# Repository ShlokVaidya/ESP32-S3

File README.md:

# ESP32-S3

Unfortunately the parts required require standard PCBA

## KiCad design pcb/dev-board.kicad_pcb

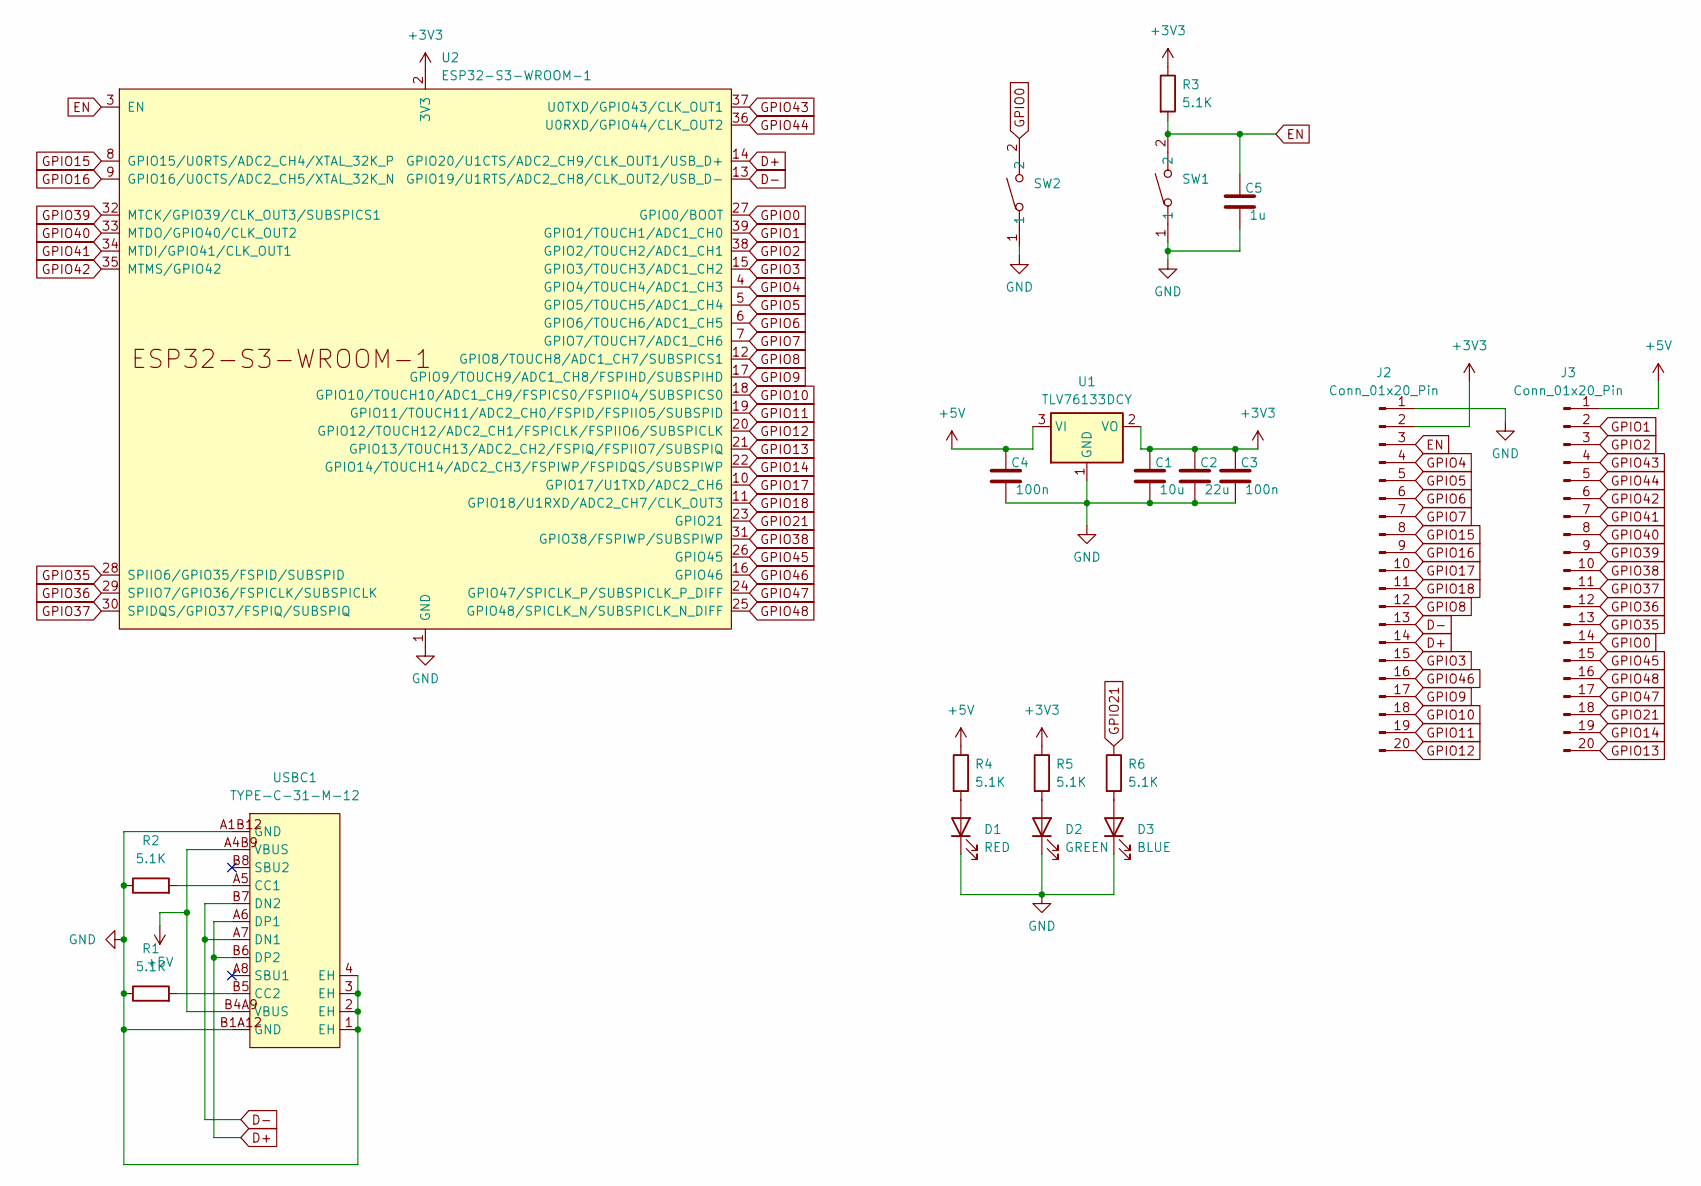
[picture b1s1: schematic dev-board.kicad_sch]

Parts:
C1: 10u; C_0603_1608Metric
C2: 22u; C_0603_1608Metric
C3, C4: 100n; C_0603_1608Metric
C5: 1u; C_0603_1608Metric
D1: RED; LED_0603_1608Metric
D2: GREEN; LED_0603_1608Metric
D3: BLUE; LED_0603_1608Metric
J2, J3: Conn_01x20_Pin; PinHeader_1x20_P2.54mm_Vertical
R1, R2, R3, R4, R5, R6: 5.1K; R_0603_1608Metric
SW1, SW2: TS-1088-AR02016; SW-SMD_L3.9-W3.0-P4.45; LCSC Part C720477
U1: TLV76133DCY; SOT-223-3_TabPin2
U2: ESP32-S3-WROOM-1
USBC1: TYPE-C-31-M-12; USB-C_SMD-TYPE-C-31-M-12_1; LCSC Part C165948

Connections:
+3V3: C1.1, C2.1, C3.1, J2.2, R3.1, R5.1, U1.2 (VO), U2.2 (3V3)
+5V: C4.1, J3.1, R4.1, U1.3 (VI), USBC1.A4B9 (VBUS), USBC1.B4A9 (VBUS)
D+: J2.14, U2.14 (GPIO20/U1CTS/ADC2_CH9/CLK_OUT1/USB_D+), USBC1.A6 (DP1), USBC1.B6 (DP2)
D-: J2.13, U2.13 (GPIO19/U1RTS/ADC2_CH8/CLK_OUT2/USB_D-), USBC1.A7 (DN1), USBC1.B7 (DN2)
EN: C5.1, J2.3, R3.2, SW1.2, U2.3 (EN)
GND: C1.2, C2.2, C3.2, C4.2, C5.2, D1.1 (K), D2.1 (K), D3.1 (K), J2.1, R1.1, R2.1, SW1.1, SW2.1, U1.1 (GND), U2.1 (GND), U2.40 (GND), U2.41 (GND), USBC1.1 (EH), USBC1.2 (EH), USBC1.3 (EH), USBC1.4 (EH), USBC1.A1B12 (GND), USBC1.B1A12 (GND)
GPIO0: J3.14, SW2.2, U2.27 (GPIO0/BOOT)
GPIO1: J3.2, U2.39 (GPIO1/TOUCH1/ADC1_CH0)
GPIO2: J3.3, U2.38 (GPIO2/TOUCH2/ADC1_CH1)
GPIO3: J2.15, U2.15 (GPIO3/TOUCH3/ADC1_CH2)
GPIO4: J2.4, U2.4 (GPIO4/TOUCH4/ADC1_CH3)
GPIO5: J2.5, U2.5 (GPIO5/TOUCH5/ADC1_CH4)
GPIO6: J2.6, U2.6 (GPIO6/TOUCH6/ADC1_CH5)
GPIO7: J2.7, U2.7 (GPIO7/TOUCH7/ADC1_CH6)
GPIO8: J2.12, U2.12 (GPIO8/TOUCH8/ADC1_CH7/SUBSPICS1)
GPIO9: J2.17, U2.17 (GPIO9/TOUCH9/ADC1_CH8/FSPIHD/SUBSPIHD)
GPIO10: J2.18, U2.18 (GPIO10/TOUCH10/ADC1_CH9/FSPICS0/FSPIIO4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)
GPIO11: J2.19, U2.19 (GPIO11/TOUCH11/ADC2_CH0/FSPID/FSPIIO5/S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)
GPIO12: J2.20, U2.20 (GPIO12/TOUCH12/ADC2_CH1/FSPICLK/FSPIIO6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)
GPIO13: J3.20, U2.21 (GPIO13/TOUCH13/ADC2_CH2/FSPIQ/FSPIIO7/S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)
GPIO14: J3.19, U2.22 (GPIO14/TOUCH14/ADC2_CH3/FSPIWP/FSPIDQS/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)
GPIO15: J2.8, U2.8 (GPIO15/U0RTS/ADC2_CH4/XTAL_32K_P)
GPIO16: J2.9, U2.9 (GPIO16/U0CTS/ADC2_CH5/XTAL_32K_N)
GPIO17: J2.10, U2.10 (GPIO17/U1TXD/ADC2_CH6)
GPIO18: J2.11, U2.11 (GPIO18/U1RXD/ADC2_CH7/CLK_OUT3)
GPIO21: J3.18, R6.1, U2.23 (GPIO21)
GPIO35: J3.13, U2.28 (SPIIO6/GPIO35/FSPID/SUBSPID)
GPIO36: J3.12, U2.29 (SPIIO7/GPIO36/FSPICLK/SUBSPICLK)
GPIO37: J3.11, U2.30 (SPIDQS/GPIO37/FSPIQ/SUBSPIQ)
GPIO38: J3.10, U2.31 (GPIO38/FSPIWP/SUBSPIWP)
GPIO39: J3.9, U2.32 (MTCK/GPIO39/CLK_OUT3/SUBSPICS1)
GPIO40: J3.8, U2.33 (MTDO/GPIO40/CLK_OUT2)
GPIO41: J3.7, U2.34 (MTDI/GPIO41/CLK_OUT1)
GPIO42: J3.6, U2.35 (MTMS/GPIO42)
GPIO43: J3.4, U2.37 (U0TXD/GPIO43/CLK_OUT1)
GPIO44: J3.5, U2.36 (U0RXD/GPIO44/CLK_OUT2)
GPIO45: J3.15, U2.26 (GPIO45)
GPIO46: J2.16, U2.16 (GPIO46)
GPIO47: J3.17, U2.24 (GPIO47/SPICLK_P/SUBSPICLK_P_DIFF)
GPIO48: J3.16, U2.25 (GPIO48/SPICLK_N/SUBSPICLK_N_DIFF)
unnamed: D1.2 (A), R4.2
unnamed: D2.2 (A), R5.2
unnamed: D3.2 (A), R6.2
unnamed: R2.2, USBC1.A5 (CC1)
unnamed: R1.2, USBC1.B5 (CC2)

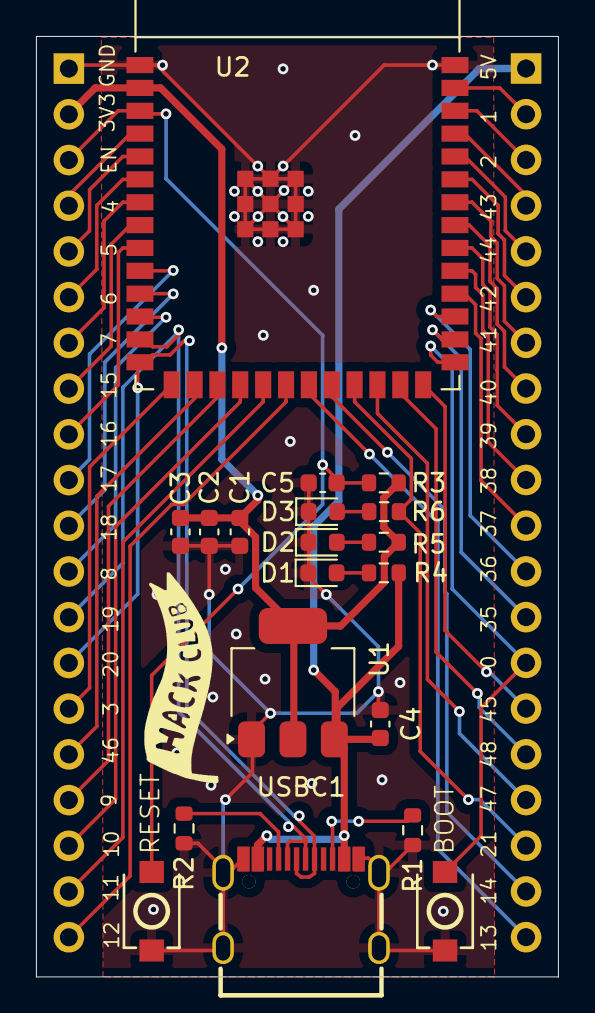
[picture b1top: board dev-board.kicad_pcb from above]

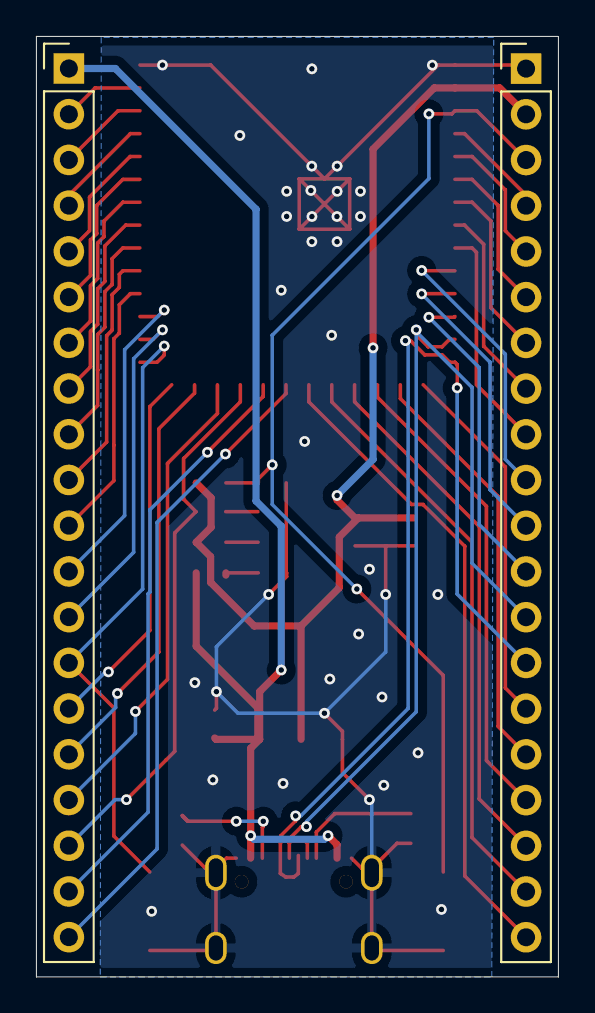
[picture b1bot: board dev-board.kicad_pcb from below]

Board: 2 copper layers, 29.0 x 52.3 mm, 21 parts (2 on the bottom side), 45 nets.

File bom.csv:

Designator,Footprint,Quantity,Value,LCSC Part #
C1,0603,1,10u,
C2,0603,1,22u,
"C3, C4",0603,2,100n,
C5,0603,1,1u,
D1,0603,1,RED,
D2,0603,1,GREEN,
D3,0603,1,BLUE,
"J2, J3",PinHeader_1x20_P2.54mm_Vertical,2,Conn_01x20_Pin,
"R1, R2, R3, R4, R5, R6",0603,6,5.1K,
"SW1, SW2",SW-SMD_L3.9-W3.0-P4.45,2,TS-1088-AR02016,C720477
U1,SOT-223-3_TabPin2,1,TLV76133DCY,
U2,ESP32-S3-WROOM-1,1,ESP32-S3-WROOM-1,
USBC1,USB-C_SMD-TYPE-C-31-M-12_1,1,TYPE-C-31-M-12,C165948

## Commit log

2025-12-01 ESP32
2025-12-03 V2.0
